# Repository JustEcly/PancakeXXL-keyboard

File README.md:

# PancakeXXL keyboard

This 40% is made in the idea of a little keyboard easy to travel with is little format and is 3d printed case to be lightweight.
This keyboard is made QMK and work with VIAL to make it customisable by everyone ! 

## Special thanks
I made it integrally but I take for inspiration for the layout the [Tanuki](https://github.com/SethSenpai/Tanuki) and get help from the [HLB team](https://github.com/H3lli0n/HLB-Projects) for some aspect of the keyboard (especially thanks to Please to help me with the PCB part and Hellion to help me with the case and firmware problems)

---
# Layout
Like say earlier I took inspiration of the Tanuki for the layout, but modify the last row by making it with a center Fn and not on the side, I also make it compatible with a 7u option.
To use the 7u layout you gonna need a special plate in the [plate and case directory](/plate_and_case/) who's using clip-in 7u stab (using 7u screw-in stab would have caused overlapping issues with switches) and activate the option on vial in the Layout tab
 ## Layout 2x2u and 7u

With the 2x2u you have an hold mod to use the up and down layer, you can customise it if you prefer to don't have it.

---
# QMK
The keyboard is made with a RP2040 MCU from rasbperry pi integrated on the PCB itself. This is a powerful MCU capable of a lot of thing like using QMK and by extension the VIAL application for easy modification of the keyboard.

---
# How to install the firmware
To install the firmware, you just need the uf2 files you can find in the [realease](https://github.com/JustEcly/PancakeXXL-keyboard/releases) or in the firmawre folder in the "[production_files](/production_files/firmware/)"
After downloading it, you need to connect the keyboard to your computer and slide the uf2 files in the directory that just open

Good job ! You now have a functionnal PCB & keyboard 👍

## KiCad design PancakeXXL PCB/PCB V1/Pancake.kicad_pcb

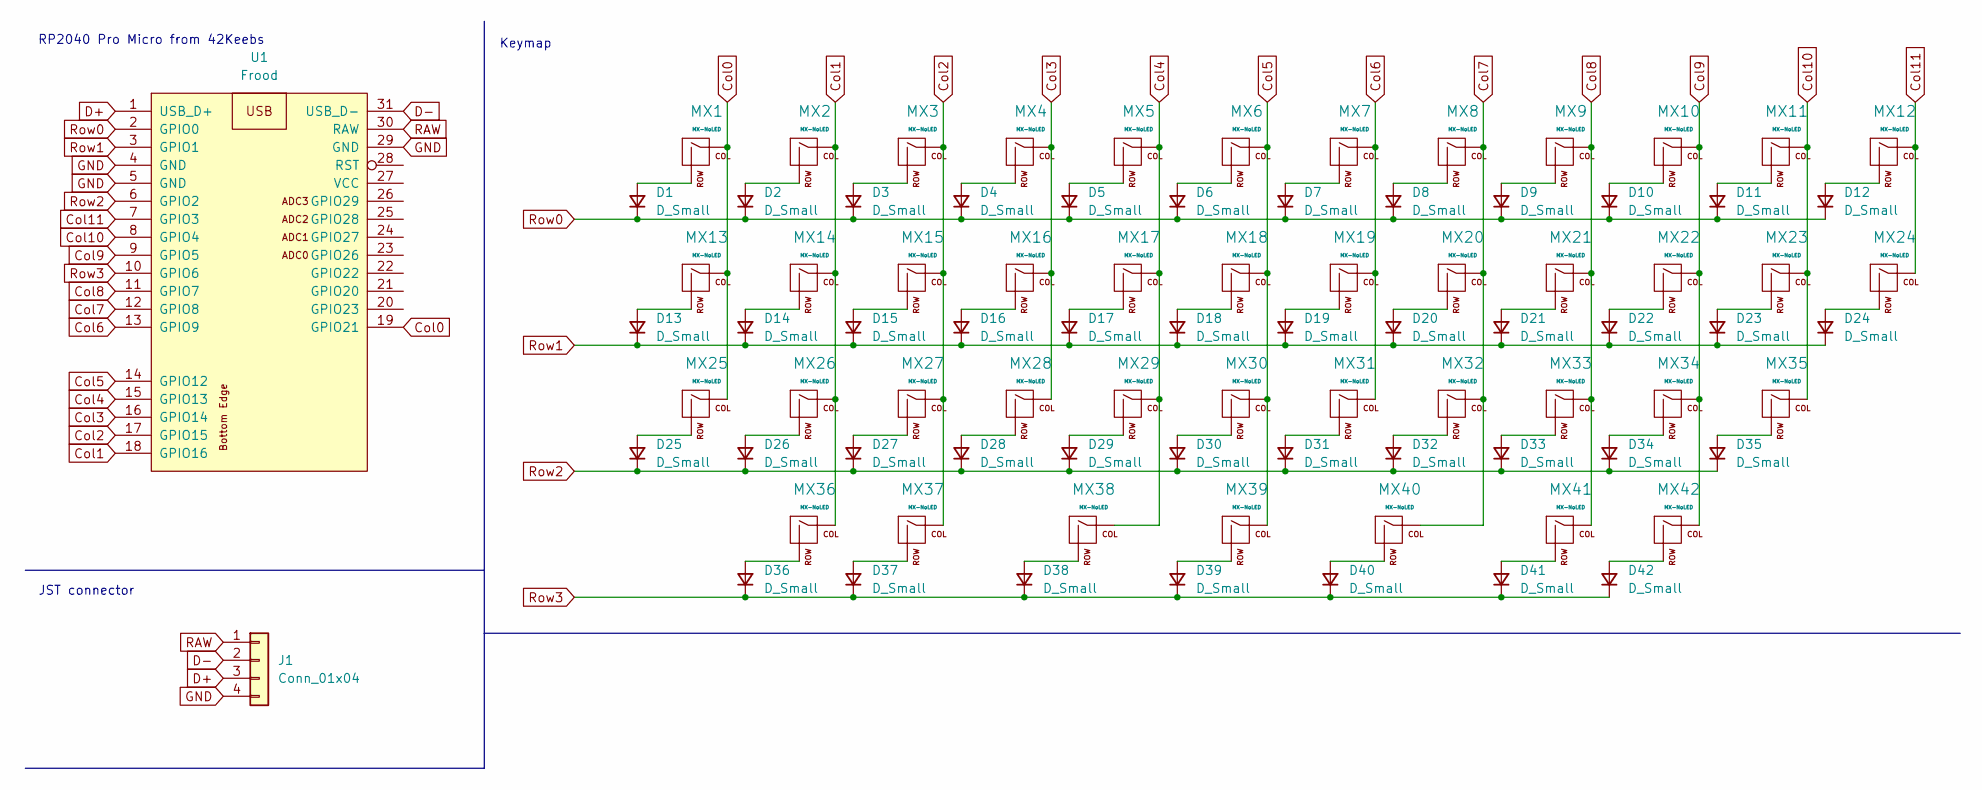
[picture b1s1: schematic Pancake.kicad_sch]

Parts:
D1, D2, D3, D4, D5, D6, D7, D8, D9, D10, D11, D12, D13, D14, D15, D16, D17, D18, D19, D20, D21, D22, D23, D24, D25, D26, D27, D28, D29, D30, D31, D32, D33, D34, D35, D36, D37, D38, D39, D40, D41, D42: D_Small; D_SOD-123
J1: Conn_01x04; JST_SH_BM04B-SRSS-TB_1x04-1MP_P1.00mm_Vertical; Part Number 1-0401FBV0T
MX1, MX2, MX3, MX4, MX5, MX6, MX7, MX8, MX9, MX10, MX11, MX14, MX15, MX16, MX17, MX18, MX19, MX20, MX21, MX22, MX23, MX24, MX26, MX27, MX28, MX29, MX30, MX31, MX32, MX33, MX34, MX37, MX39, MX41: MX-NoLED; MX_PCB_1.00u
MX12, MX13, MX35, MX36, MX42: MX-NoLED; MX_PCB_1.25u
MX25: MX-NoLED; MX_PCB_1.50u
MX38, MX40: MX-NoLED; MX_PCB_2.00u
U1: Frood; Frood_PinHeader_2x13+5_P2.54mm_Labels_Top

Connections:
Col0: MX1.1 (COL), MX13.1 (COL), MX25.1 (COL), U1.19 (GPIO21)
Col1: MX2.1 (COL), MX14.1 (COL), MX26.1 (COL), MX36.1 (COL), U1.18 (GPIO16)
Col2: MX3.1 (COL), MX15.1 (COL), MX27.1 (COL), MX37.1 (COL), U1.17 (GPIO15)
Col3: MX4.1 (COL), MX16.1 (COL), MX28.1 (COL), U1.16 (GPIO14)
Col4: MX5.1 (COL), MX17.1 (COL), MX29.1 (COL), MX38.1 (COL), U1.15 (GPIO13)
Col5: MX6.1 (COL), MX18.1 (COL), MX30.1 (COL), MX39.1 (COL), U1.14 (GPIO12)
Col6: MX7.1 (COL), MX19.1 (COL), MX31.1 (COL), U1.13 (GPIO9)
Col7: MX8.1 (COL), MX20.1 (COL), MX32.1 (COL), MX40.1 (COL), U1.12 (GPIO8)
Col8: MX9.1 (COL), MX21.1 (COL), MX33.1 (COL), MX41.1 (COL), U1.11 (GPIO7)
Col9: MX10.1 (COL), MX22.1 (COL), MX34.1 (COL), MX42.1 (COL), U1.9 (GPIO5)
Col10: MX11.1 (COL), MX23.1 (COL), MX35.1 (COL), U1.8 (GPIO4)
Col11: MX12.1 (COL), MX24.1 (COL), U1.7 (GPIO3)
D+: J1.3, U1.1 (USB_D+)
D-: J1.2, U1.31 (USB_D-)
GND: J1.4, U1.4 (GND), U1.5 (GND), U1.29 (GND)
unnamed: D1.2 (A), MX1.2 (ROW)
unnamed: D2.2 (A), MX2.2 (ROW)
unnamed: D3.2 (A), MX3.2 (ROW)
unnamed: D4.2 (A), MX4.2 (ROW)
unnamed: D5.2 (A), MX5.2 (ROW)
unnamed: D6.2 (A), MX6.2 (ROW)
unnamed: D7.2 (A), MX7.2 (ROW)
unnamed: D8.2 (A), MX8.2 (ROW)
unnamed: D9.2 (A), MX9.2 (ROW)
unnamed: D10.2 (A), MX10.2 (ROW)
unnamed: D11.2 (A), MX11.2 (ROW)
unnamed: D12.2 (A), MX12.2 (ROW)
unnamed: D13.2 (A), MX13.2 (ROW)
unnamed: D14.2 (A), MX14.2 (ROW)
unnamed: D15.2 (A), MX15.2 (ROW)
unnamed: D16.2 (A), MX16.2 (ROW)
unnamed: D17.2 (A), MX17.2 (ROW)
unnamed: D18.2 (A), MX18.2 (ROW)
unnamed: D19.2 (A), MX19.2 (ROW)
unnamed: D20.2 (A), MX20.2 (ROW)
unnamed: D21.2 (A), MX21.2 (ROW)
unnamed: D22.2 (A), MX22.2 (ROW)
unnamed: D23.2 (A), MX23.2 (ROW)
unnamed: D24.2 (A), MX24.2 (ROW)
unnamed: D25.2 (A), MX25.2 (ROW)
unnamed: D26.2 (A), MX26.2 (ROW)
unnamed: D27.2 (A), MX27.2 (ROW)
unnamed: D28.2 (A), MX28.2 (ROW)
unnamed: D29.2 (A), MX29.2 (ROW)
unnamed: D30.2 (A), MX30.2 (ROW)
unnamed: D31.2 (A), MX31.2 (ROW)
unnamed: D32.2 (A), MX32.2 (ROW)
unnamed: D33.2 (A), MX33.2 (ROW)
unnamed: D34.2 (A), MX34.2 (ROW)
unnamed: D35.2 (A), MX35.2 (ROW)
unnamed: D36.2 (A), MX36.2 (ROW)
unnamed: D37.2 (A), MX37.2 (ROW)
unnamed: D38.2 (A), MX38.2 (ROW)
unnamed: D39.2 (A), MX39.2 (ROW)
unnamed: D40.2 (A), MX40.2 (ROW)
unnamed: D41.2 (A), MX41.2 (ROW)
unnamed: D42.2 (A), MX42.2 (ROW)
RAW: J1.1, U1.30 (RAW)
Row0: D1.1 (K), D2.1 (K), D3.1 (K), D4.1 (K), D5.1 (K), D6.1 (K), D7.1 (K), D8.1 (K), D9.1 (K), D10.1 (K), D11.1 (K), D12.1 (K), U1.2 (GPIO0)
Row1: D13.1 (K), D14.1 (K), D15.1 (K), D16.1 (K), D17.1 (K), D18.1 (K), D19.1 (K), D20.1 (K), D21.1 (K), D22.1 (K), D23.1 (K), D24.1 (K), U1.3 (GPIO1)
Row2: D25.1 (K), D26.1 (K), D27.1 (K), D28.1 (K), D29.1 (K), D30.1 (K), D31.1 (K), D32.1 (K), D33.1 (K), D34.1 (K), D35.1 (K), U1.6 (GPIO2)
Row3: D36.1 (K), D37.1 (K), D38.1 (K), D39.1 (K), D40.1 (K), D41.1 (K), D42.1 (K), U1.10 (GPIO6)

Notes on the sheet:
JST connector
RP2040 Pro Micro from 42Keebs
Keymap

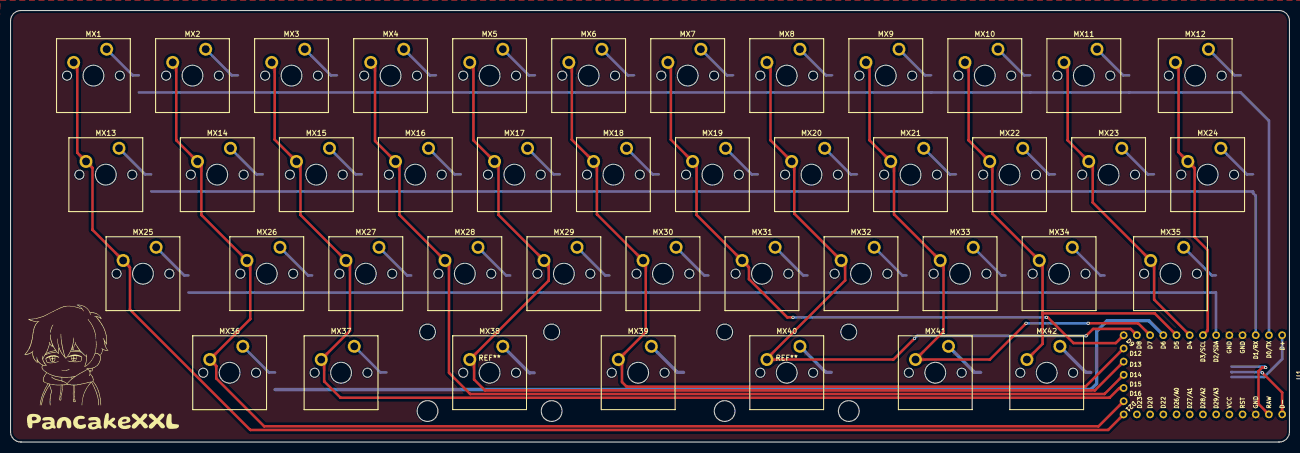
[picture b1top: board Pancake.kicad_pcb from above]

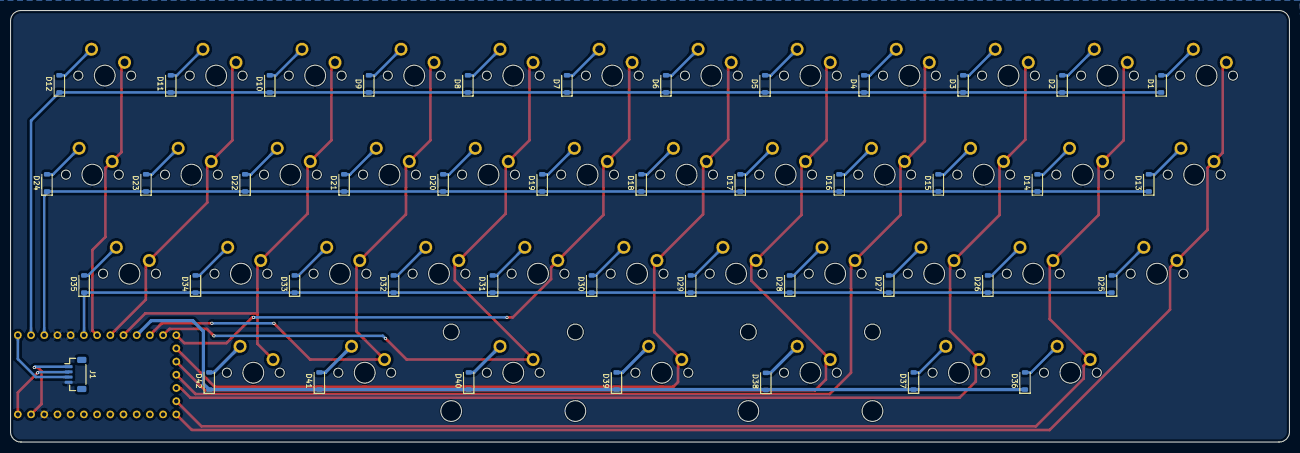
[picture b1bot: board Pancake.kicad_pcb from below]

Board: 2 copper layers, 246.0 x 83.0 mm, 86 parts (43 on the bottom side), 62 nets.

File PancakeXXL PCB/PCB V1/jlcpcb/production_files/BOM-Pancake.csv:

Comment,Designator,Footprint,LCSC,Quantity
Conn_01x04,J1,JST_SH_BM04B-SRSS-TB_1x04-1MP_P1.00mm_Vertical,C160390,1
D_Small,"D1,D10,D11,D12,D13,D14,D15,D16,D17,D18,D19,D2,D20,D21,D22,D23,D24,D25,D26,D27,D28,D29,D3,D30,D31,D32,D33,D34,D35,D36,D37,D38,D39,D4,D40,D41,D42,D5,D6,D7,D8,D9",D_SOD-123,C7370889,42
MX-NoLED,MX16,MX_PCB_1.00u,,1
MX-NoLED,MX32,MX_PCB_1.00u,,1
Frood,U1,Frood_PinHeader_2x13+5_P2.54mm_Labels_Top,,1
MX-NoLED,MX12,MX_PCB_1.25u,,1
MX-NoLED,MX6,MX_PCB_1.00u,,1
MX-NoLED,MX27,MX_PCB_1.00u,,1
MX-NoLED,MX35,MX_PCB_1.25u,,1
MX-NoLED,MX38,MX_PCB_2.00u,,1
MX-NoLED,MX28,MX_PCB_1.00u,,1
MX-NoLED,MX40,MX_PCB_2.00u,,1
MX-NoLED,MX1,MX_PCB_1.00u,,1
MX-NoLED,MX31,MX_PCB_1.00u,,1
MX-NoLED,MX36,MX_PCB_1.25u,,1
MX-NoLED,MX42,MX_PCB_1.25u,,1
MX-NoLED,MX26,MX_PCB_1.00u,,1
MX-NoLED,MX34,MX_PCB_1.00u,,1
MX-NoLED,MX37,MX_PCB_1.00u,,1
MX-NoLED,MX10,MX_PCB_1.00u,,1
MX-NoLED,MX20,MX_PCB_1.00u,,1
MX-NoLED,MX30,MX_PCB_1.00u,,1
MX-NoLED,MX23,MX_PCB_1.00u,,1
MX-NoLED,MX13,MX_PCB_1.25u,,1
MX-NoLED,MX2,MX_PCB_1.00u,,1
MX-NoLED,MX18,MX_PCB_1.00u,,1
MX-NoLED,MX24,MX_PCB_1.00u,,1
MX-NoLED,MX7,MX_PCB_1.00u,,1
MX-NoLED,MX5,MX_PCB_1.00u,,1
MX-NoLED,MX33,MX_PCB_1.00u,,1
MX-NoLED,MX4,MX_PCB_1.00u,,1
MX-NoLED,MX11,MX_PCB_1.00u,,1
MX-NoLED,MX9,MX_PCB_1.00u,,1
MX-NoLED,MX19,MX_PCB_1.00u,,1
MX-NoLED,MX14,MX_PCB_1.00u,,1
MX-NoLED,MX39,MX_PCB_1.00u,,1
MX-NoLED,MX17,MX_PCB_1.00u,,1
MX-NoLED,MX22,MX_PCB_1.00u,,1
MX-NoLED,MX41,MX_PCB_1.00u,,1
MX-NoLED,MX21,MX_PCB_1.00u,,1
MX-NoLED,MX8,MX_PCB_1.00u,,1
MX-NoLED,MX29,MX_PCB_1.00u,,1
MX-NoLED,MX3,MX_PCB_1.00u,,1
MX-NoLED,MX15,MX_PCB_1.00u,,1
MX-NoLED,MX25,MX_PCB_1.50u,,1

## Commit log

2025-01-31 Kicad files
    Statring to create the kicad files
2025-02-02 Strart the schematics
2025-02-10 KLE and Datasheet
    Add to the folder the datasheet of the RP2040 Pro Micro controller and the Keyboard Layout Editor files
2025-02-10 README
    Start to write the README files
2025-02-11 Lib modification
    I change my library for my micro controller to use the RP2040 Pro Micro from 42Keebs
2025-02-13 A lot of modification
    addition of a jst cable and other
2025-02-24 Many change
2025-03-09 Modification complète du PCB et fichier de production
    Flemme de faire en anglais au pire google traduction ça existe 😭
    J'ai complètement refait le pcb pour mettre les diodes derrière et donc refait tout le routing, en plus de ça j'ai fait les fichier pour faire produire le pcb par jlcpcb donc vous pourrez aussi le pr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
2025-03-15 Creation of the case and the plate
    STEP and STL
2025-03-17 Mise à jour des STL et STEP
    J'ai du retravailler la case alors voici les nouvelles modification de bottom case, top case et plate
2025-03-25 Pleins de modif sur la case
    Pleins de petite modification pour améliorer la case en général
2025-03-25 Plate 7u Clip-in
    Ajout d'une plate 7u en cilp-in pour les fans de 7u
2025-03-27 Ajout du KLE 7u
2025-04-16 Image ajouter
    J'ai rajouter les images du clavier fait dans fusion 360
2025-04-16 README to README_FR
    I set the README files in french to write it easier and add later an english version for everyone.
2025-04-23 Top V2
    Mise à jour de la case pour évitez les problèmes avec le micro controller
2025-04-26 Start of the QMK part
2025-04-28 QMK-Vial make
    Il finish to make the Vial and QMK code
2025-05-22 PCB last modification
2025-06-09 Update to pcb v2
2025-08-08 Update QMK
    I update the qmk for the new pcb
2025-10-23 Mise à jour README
2025-12-01 C'était pas droit avant, mainteant le pcb et le KLE l'ai faut que je fasse la plate et la case mtn
2025-12-07 Rectification KLE, 3D
    J'ai refait tout le design pour que cette fois-ci tout soit bien droit
2025-12-08 Modification plate clip-in
    Je l'ai es modifier sous conseil de Bagri pour les rendre plus solide
2025-12-15 Léger ajustement
2026-01-21 fix: vial and qmk fixes : - path must be lowercase - mcu pins don't have 0 below 10 - vial json clean - keymap were not correctly written - qmk layouts are either LAYOUT or one of the community ones
2026-03-03 update after many month
    Final design of the case,
    Final plate design,
    Final PCB for production,
    And many more
2026-03-03 README update
    I update the readme files to make it in english
2026-03-03 Production files update
    everytings needed to make the keyboard can be find in the general production files
2026-03-04 an another readme update
    add some modification to the readme.md and add one in the production_files/firmawre/
2026-03-04 Problem with readme
    I patched a bug with the video of the firmware
2026-03-04 Update README.md
    another one bug in the display
2026-03-04 Update README.md
    start to casse me les couilles hein
